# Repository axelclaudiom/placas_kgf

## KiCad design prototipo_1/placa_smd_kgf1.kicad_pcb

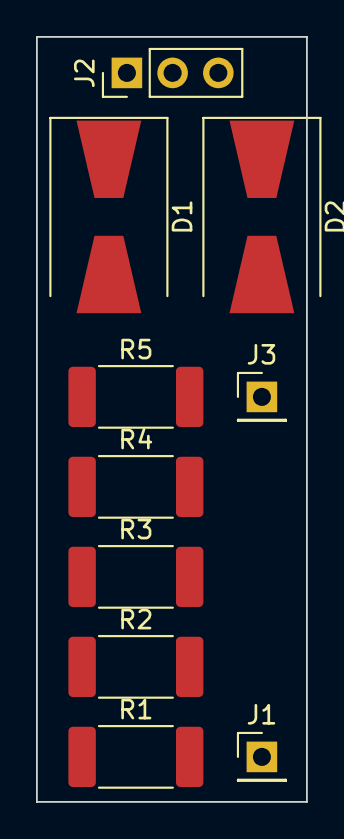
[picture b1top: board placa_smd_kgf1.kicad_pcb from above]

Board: 2 copper layers, 15.0 x 42.5 mm, 10 parts (0 on the bottom side), 4 nets, no tracks yet.

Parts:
D1, D2: D; D_SMB-SMC_Universal_Handsoldering
J1, J3: Conn_01x01_Female; PinHeader_1x01_P2.54mm_Vertical
J2: Conn_01x03_Female; PinHeader_1x03_P2.54mm_Vertical
R1, R2, R3, R4, R5: 22R; R_2512_6332Metric_Pad1.52x3.35mm_HandSolder

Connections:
unnamed: D1.1, D2.1, J2.1, J2.2, J2.3
unnamed: D1.2, R1.1, R2.1, R3.1, R4.1, R5.1
unnamed: D2.2, J3.1
unnamed: J1.1, R1.2, R2.2, R3.2, R4.2, R5.2

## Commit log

2022-03-26 prueba
2022-03-26 prototipo_1
2022-03-26 prototipo_2
2022-04-05 Actualizacion de prototipo
